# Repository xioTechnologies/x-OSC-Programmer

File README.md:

x-OSC-Programmer
================

Adapter for programming [x-OSCs](http://www.x-io.co.uk/products/x-osc/) with ICSP.  Designed to be assembled from two copies of the PCB separated by three [spacers](http://uk.rs-online.com/web/p/round-spacers/2652192/) with the [reset button](http://uk.rs-online.com/web/p/tactile-switches/7831252/) and power LED mounted on the top board.  Electrical connections between the PCBs are made through the [pogo pins](https://www.sparkfun.com/products/9174).  Also features header for [FTDI USB serial converter](https://www.sparkfun.com/products/9716) which can also be used to power x-OSC via USB.

PCB with black solder mask and yellow silkscreen was ordered from [pcbpanel](http://www.pcbpanel.co.uk/browse-and-buy-pcb-panels.html?page=shop.product_details&flypage=shop.flypage&product_id=21&category_id=7).

Fully Assembled
---------------

<div align="center">

</div>

<div align="center">

</div>

Prototype Design
----------------

<div align="center">

</div>

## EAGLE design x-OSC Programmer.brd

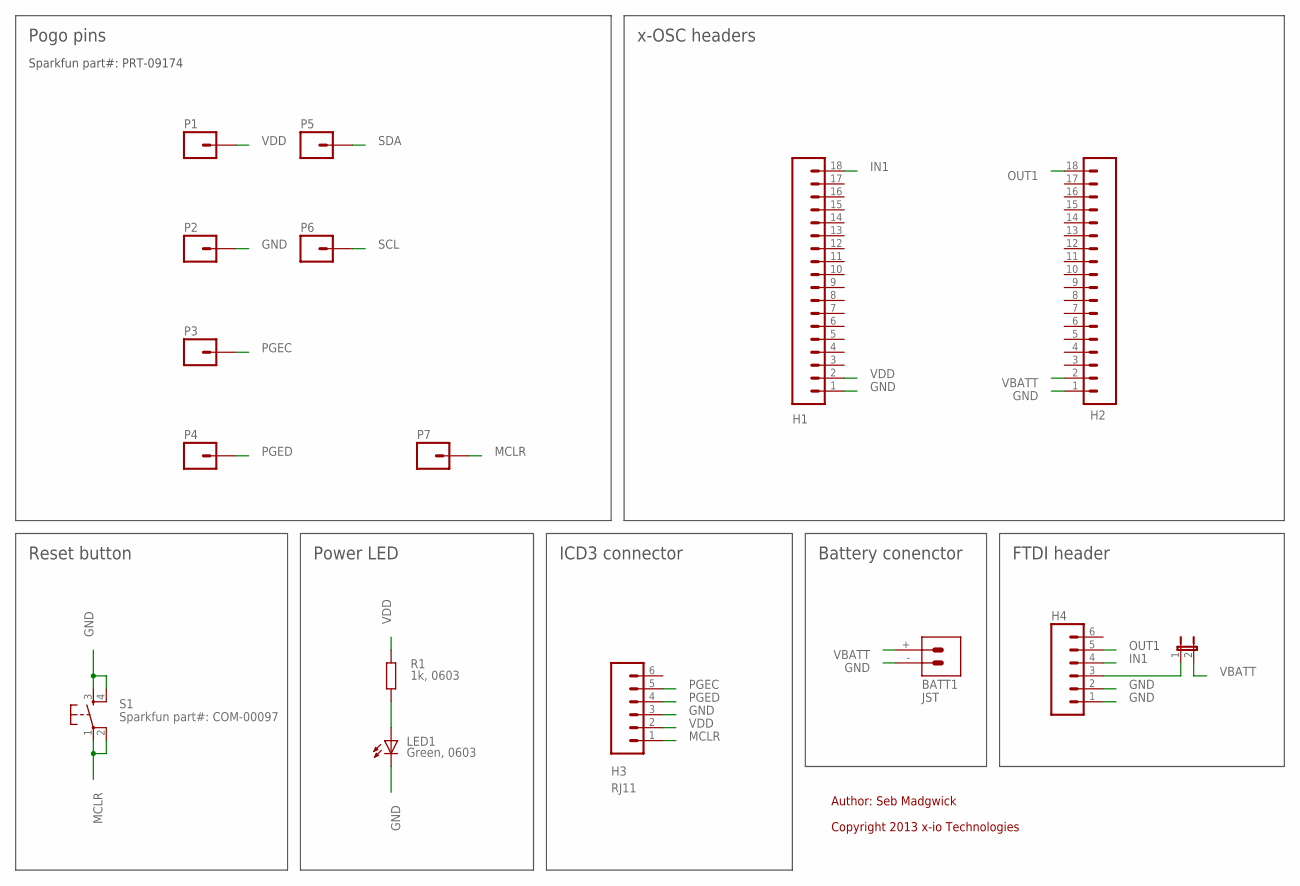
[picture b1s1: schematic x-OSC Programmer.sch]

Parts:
BATT1: JST; JST-R/A
H1, H2: M18_; 1X18
H3: RJ11; RJ11-6
H4: M06SIP; 1X06
JP1: JUMPER-2SMD-NO; SJ_2S-NO
LED1: Green, 0603; LED-0603
P1, P2, P3, P4, P5, P6, P7: M01PTH; 1X01
R1: 1k, 0603; R0402
S1: Sparkfun part#: COM-00097; TACTILE-PTH

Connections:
GND: BATT1.-, H1.1, H2.1, H3.3, H4.1, H4.2, LED1.C, P2.1, S1.3, S1.4
IN1: H1.18, H4.4
MCLR: H3.1, P7.1, S1.1, S1.2
unnamed: LED1.A, R1.2
unnamed: H4.3, JP1.1
OUT1: H2.18, H4.5
PGEC: H3.5, P3.1
PGED: H3.4, P4.1
SCL: P6.1
SDA: P5.1
VBATT: BATT1.+, H2.2, JP1.2
VDD: H1.2, H3.2, P1.1, R1.1

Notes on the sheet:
Copyright 2013 x-io Technologies
Author: Seb Madgwick
Pogo pins
Sparkfun part#: PRT-09174
x-OSC headers
Reset button
Power LED
Battery conenctor
ICD3 connector
FTDI header

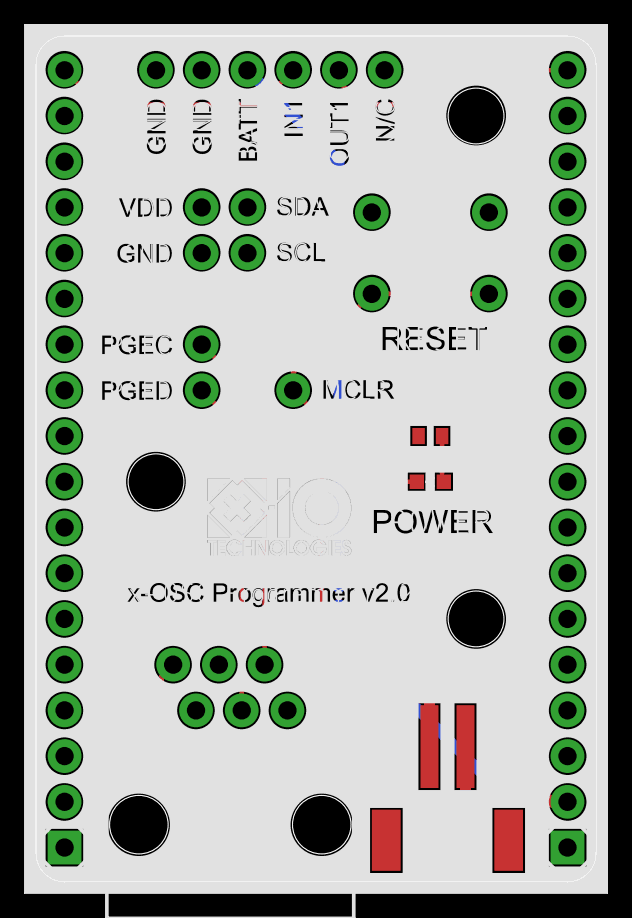
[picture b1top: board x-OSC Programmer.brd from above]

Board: 2 copper layers, 31.1 x 47.0 mm, 18 parts (1 on the bottom side), 10 nets.

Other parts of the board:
U$1: X-IO_TECHNOLOGIES_LOGO_8MM_TOP
U$2: X-OSC_PROGRAMMER_V2.0_SILKSCREEN

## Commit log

2013-10-25 Redesign for x-OSC v1.3
2013-10-25 Add photo of prototype
2013-10-25 Add FTDI header
2013-10-28 Remove unwanted .gpi file
2013-11-04 Add photos
